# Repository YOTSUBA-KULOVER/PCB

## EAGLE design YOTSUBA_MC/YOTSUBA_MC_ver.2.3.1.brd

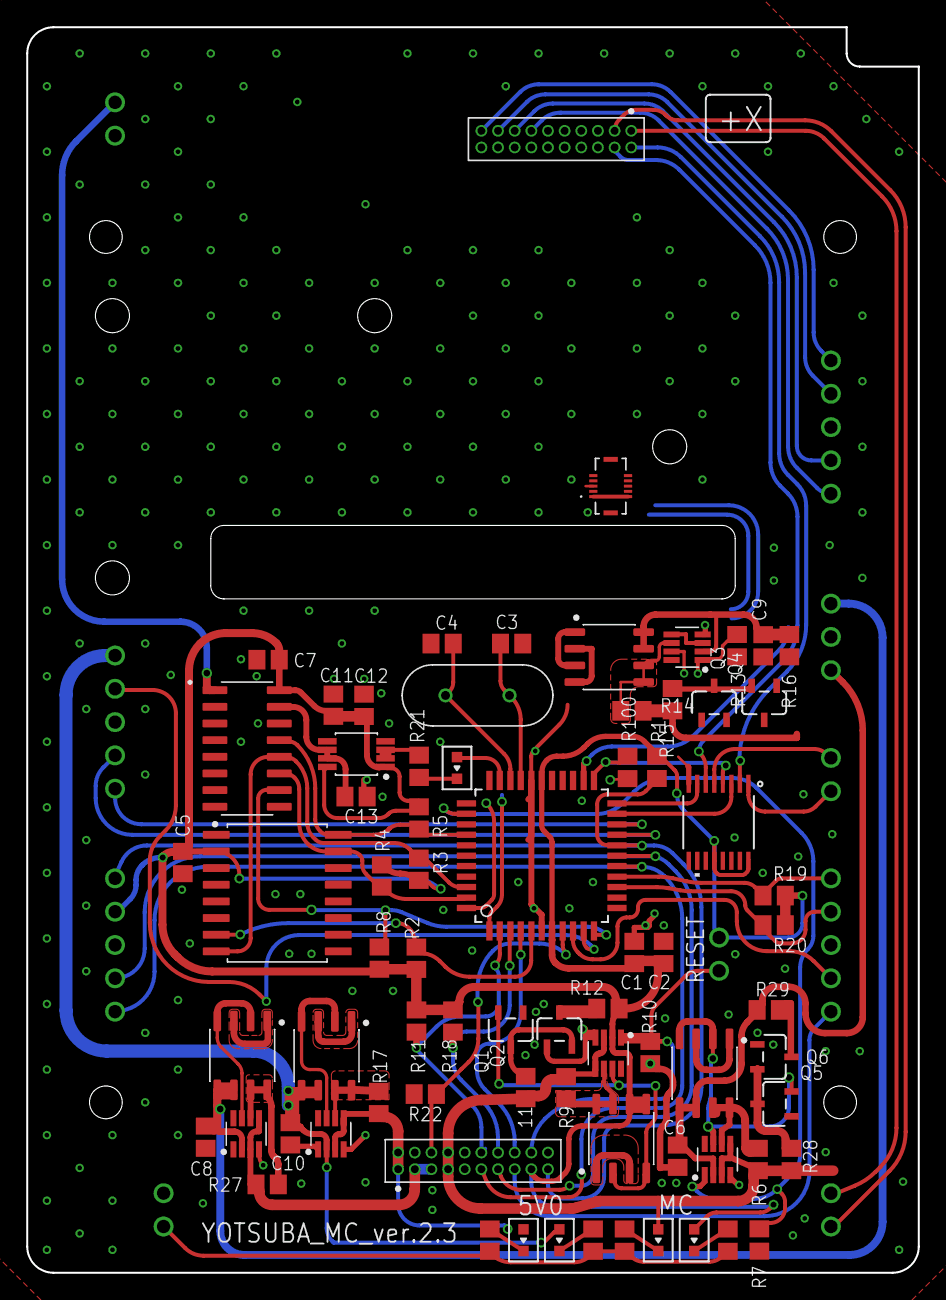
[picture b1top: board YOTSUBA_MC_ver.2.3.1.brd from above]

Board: 2 copper layers, 68.0 x 95.0 mm, 84 parts (0 on the bottom side), 78 nets.

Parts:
11: R2012
C1, C2, C3, C4, C5, C6, C7, C8, C10, C11, C12, C13: 10μ; C2012
C9: 10μ; R2012
COM_MAG: 1X05
IND: 1X02
J1: DF37NB-10DS-0.4V(51); HRS_DF37NB-10DS-0.4V(51)
JP4: 1X02
MAG_PWR: 1X03
PANEL: 1X05
PROGRAM: 1X05
Q1, Q2, Q3, Q4, Q5, Q6: BSS138BKT116SOT23_BSS138_ROM-M; SOT23_BSS138_ROM-M
R1, R2, R3, R4, R5, R6, R7, R8, R10, R11, R12, R13, R14, R15, R16, R17, R18, R19, R20, R21, R22, R23, R24, R25, R26, R27, R28, R29: R2012
R9: 0.025; R2012
R100: 100k; R2012
RPI: 1X05
U1: MAX4702EUE+; 21-0066J_16
U2: MCP3208-CI/SL; SOIC127P600X175-16N
U$1: MT25QL512_16SOP2; SOIC127P1032X265-16N
U$2, U$7, U$9, U$10, U$13: DMG6898LSD; SOIC127P600X150-8N
U$3, U$8, U$11, U$12, U$14: LTC4361; SOP65P280X100-8N
U$4: PIC18LF4620-I/PT; QFP80P1200X1200X120-44N
U$16, U$20, U$26: 1X02
U$17, U$22: M50-3001045
U$18, U$21, U$23, U$24, U$25: LED_1608
U$19: ADR35XX; SOP65P490X110-8N
Y1: HC-49/U-S16000000ABJB; XTAL_HC49P488W43L1150T466H350

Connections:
3V3: 11.1, R6.2, R9.2, R14.2, R15.1, R28.1, U$3.GATEP, U$3.IN, U$8.GATEP, U$8.IN, U$11.GATEP, U$11.IN, U$17.7, U$17.8, U$23.A
3V3_MAG: C6.2, MAG_PWR.1, R29.1, U$2.D1$1, U$2.D1$2, U$3.OUT
3V3_MC_EL: C1.1, C2.1, C5.2, C7.2, C11.2, C12.2, JP4.1, PROGRAM.2, R1.2, R2.2, R3.2, R4.2, R5.2, R8.1, R11.2, R12.1, R18.2, R19.2, R20.2, U1.12, U1.16, U2.16, U$1.VCC, U$4.7, U$4.28, U$7.D1$1, U$7.D1$2, U$8.OUT, U$17.17, U$19.ENABLE, U$19.VIN, U$21.A
3V3_MC_GNSS: C9.2, J1.1, J1.2, R16.1, U$10.D2$1, U$10.D2$2, U$11.OUT
5V0: R17.2, U$14.GATEP, U$14.IN, U$17.1, U$17.2, U$25.A
5V0_MC_RPI: C10.2, RPI.1, U$13.D1$1, U$13.D1$2, U$14.OUT, U$24.A
7V0: R27.2, U$12.GATEP, U$12.IN, U$17.3, U$17.5
7V0_MAG: C8.2, MAG_PWR.3, U$9.D1$1, U$9.D1$2, U$12.OUT
CS_ADC: R8.2, U2.10, U$4.11
GND: C1.2, C2.2, C3.2, C4.2, C5.1, C6.1, C7.1, C8.1, C9.1, C10.1, C11.1, C12.1, C13.2, COM_MAG.3, IND.2, J1.4, J1.6, J1.8, J1.S1, J1.S2, MAG_PWR.2, PANEL.3, PROGRAM.3, Q1.1, Q2.1, Q3.1, Q4.1, Q5.1, Q6.1, R7.2, R10.2, R13.2, R21.1, R22.1, R100.1, RPI.3, U1.8, U2.9, U2.14, U$1.VSS, U$3.GND, U$4.6, U$4.29, U$8.GND, U$11.GND, U$12.GND, U$12.ON, U$14.GND, U$14.ON, U$17.4, U$17.9, U$17.10, U$19.GND_FORCE, U$19.GND_SENSE, U$22.5, U$22.6, U$22.7, U$22.8, U$22.9, U$22.10, U$22.11, U$22.12, U$22.14, U$22.16, U$22.18, U$22.20, U$26.2
INDI: U$4.32, U$18.A
INT<<MAG: COM_MAG.2, U$4.9
INT<<MAIN: R22.2, U$4.8, U$17.6
INT<<RPI: RPI.2, U$4.10
INT>>MAIN: U$4.4, U$17.16
MCLR_MAG: PANEL.5, U$22.19
MCLR_MC: PROGRAM.1, R1.1, U$4.18, U$17.19
MC_SPI_CLK: R5.1, U2.13, U$1.C, U$4.37
MC_SPI_MISO: R3.1, U2.12, U$1.DQ1, U$4.42
MC_SPI_MOSI: R4.1, U2.11, U$1.DQ0, U$4.43
unnamed: R23.2, U$21.C
unnamed: C3.1, U$4.30, Y1.2
unnamed: R24.2, U$23.C
unnamed: C4.1, U$4.31, Y1.1
unnamed: R25.2, U$24.C
unnamed: R26.2, U$25.C
unnamed: R2.1, U$1.S#, U$4.5
unnamed: IND.1, R23.1, R24.1, R25.1, R26.1
unnamed: U$2.S1, U$2.S2
unnamed: R6.1, U$2.D2$1, U$2.D2$2, U$3.SENSE
unnamed: Q5.2, U$2.G1, U$2.G2, U$3.GATE
unnamed: Q5.3, Q6.2, R28.2
unnamed: U$9.S1, U$9.S2
unnamed: R21.2, U$18.C
unnamed: R27.1, U$9.D2$1, U$9.D2$2, U$12.SENSE
unnamed: U$9.G1, U$9.G2, U$12.GATE
unnamed: Q6.3, R29.2
unnamed: U$7.S1, U$7.S2
unnamed: R9.1, U$7.D2$1, U$7.D2$2, U$8.SENSE
unnamed: Q1.2, U$7.G1, U$7.G2, U$8.GATE
unnamed: 11.2, Q1.3, Q2.2
unnamed: Q2.3, R12.2
unnamed: U$10.S1, U$10.S2
unnamed: R14.1, U$10.D1$1, U$10.D1$2, U$11.SENSE
unnamed: Q3.2, U$10.G1, U$10.G2, U$11.GATE
unnamed: Q3.3, Q4.2, R15.2
unnamed: Q4.3, R16.2
unnamed: U$13.S1, U$13.S2
unnamed: R17.1, U$13.D2$1, U$13.D2$2, U$14.SENSE
unnamed: U$13.G1, U$13.G2, U$14.GATE
OUT0_ADC: U2.1, U$26.1
PGC_MAG: PANEL.1, U$22.13
PGC_MC: PROGRAM.5, U$4.16, U$17.11
PGD_MAG: PANEL.2, U$22.15
PGD_MC: PROGRAM.4, U$4.17, U$17.13
RESET_MAG: COM_MAG.1, U$17.15
RESET_MAG_EXT: R7.1, U$3.ON, U$4.35
RESET_MC_EL: JP4.2, R10.1, U$8.ON, U$17.18
RESET_MC_GNSS: R13.1, U$4.24, U$11.ON
RPI_EPS_IO_1: U$20.1, U$22.1
RPI_EPS_IO_2: U$20.2, U$22.3
RX_GNSS: J1.3, U$4.44
RX_MC_TX_MAG: COM_MAG.4, R20.1, U$4.14
RX_MC_TX_MAIN: R18.1, U$4.3, U$17.14
RX_MC_TX_RPI: RPI.4, U$4.19
SELECT: R100.2, U1.4, U$4.23
TRCLK>>COM: U1.2, U$22.2
TRCLK_MC: U1.3, U$4.21
TRCLK_RPI: U1.1, U$16.1
TRDAT>>COM: U1.6, U$22.4
TRDAT_MC: U1.7, U$4.22
TRDAT_RPI: U1.5, U$16.2
TX_GNSS: J1.5, U$4.1
TX_MC_RX_MAG: COM_MAG.5, R19.1, U$4.15
TX_MC_RX_MAIN: R11.1, U$4.2, U$17.12
TX_MC_RX_RPI: RPI.5, U$4.20
VDD_MAG: PANEL.4, U$22.17
VREF_2V5: C13.1, U2.15, U$19.VOUT_FORCE, U$19.VOUT_SENSE

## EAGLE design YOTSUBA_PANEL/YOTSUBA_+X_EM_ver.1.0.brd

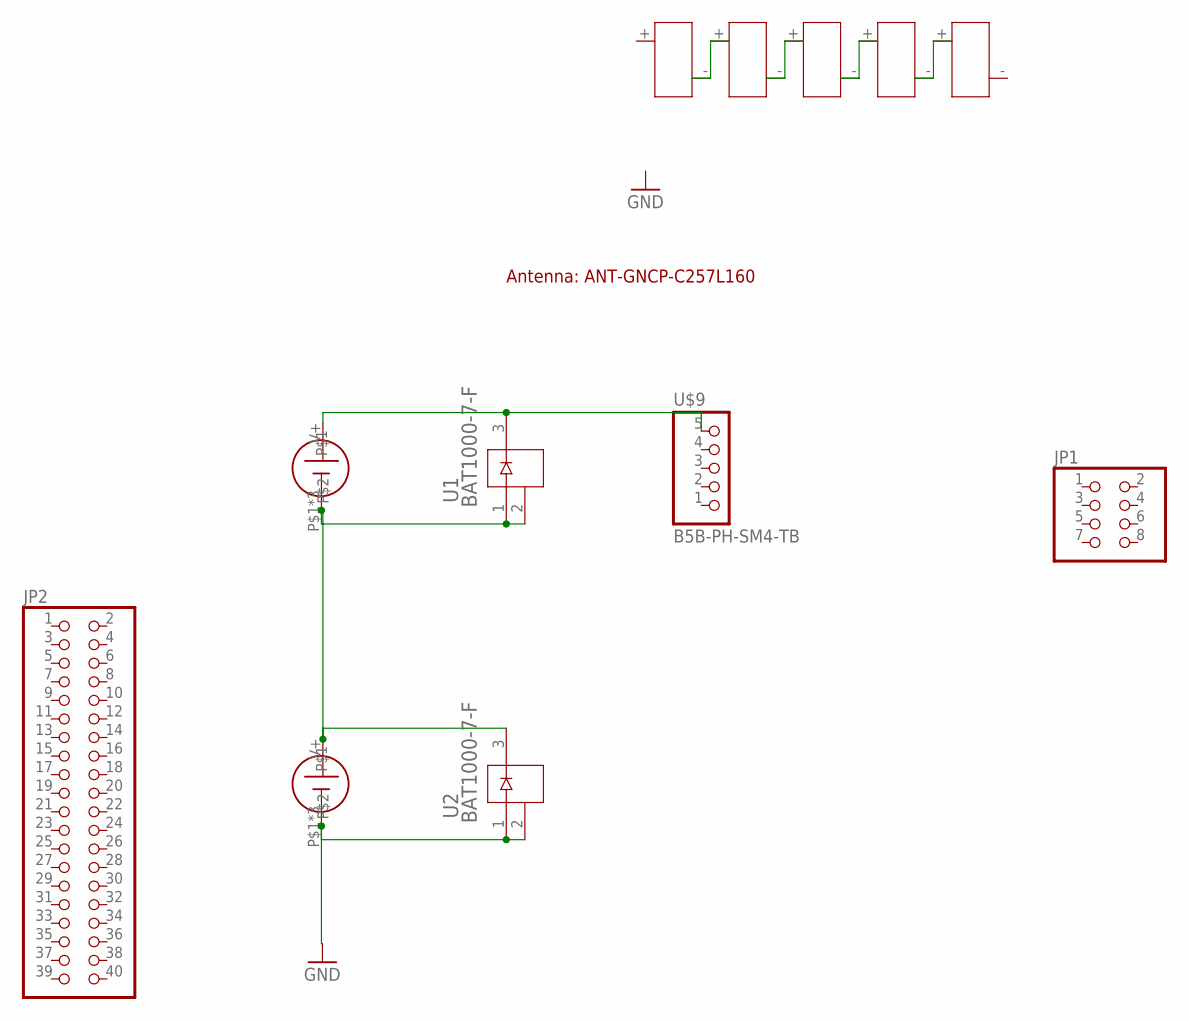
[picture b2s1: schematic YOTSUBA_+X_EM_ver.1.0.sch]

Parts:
JP1: PINHD-2X4; 2X04
JP2: PINHD-2X20; 2X20
U1, U2: BAT1000-7-F; SOT23_BAT_DIO
U$1, U$8: SOLAR_2.0_SOLAR
U$2: ANT-GNCP-C257L160
U$3, U$4, U$5, U$6, U$7: KSP-F12
U$9: B5B-PH-SM4-TB

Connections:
GND: U2.1, U2.2, U$8.P$1, U$8.P$2, U$8.P$3
unnamed: U$3.-, U$4.+
unnamed: U$4.-, U$5.+
unnamed: U$5.-, U$6.+
unnamed: U$6.-, U$7.+
unnamed: U1.1, U1.2, U2.3, U$1.P$1, U$1.P$2, U$1.P$3, U$8.V+
unnamed: U1.3, U$1.V+, U$9.5

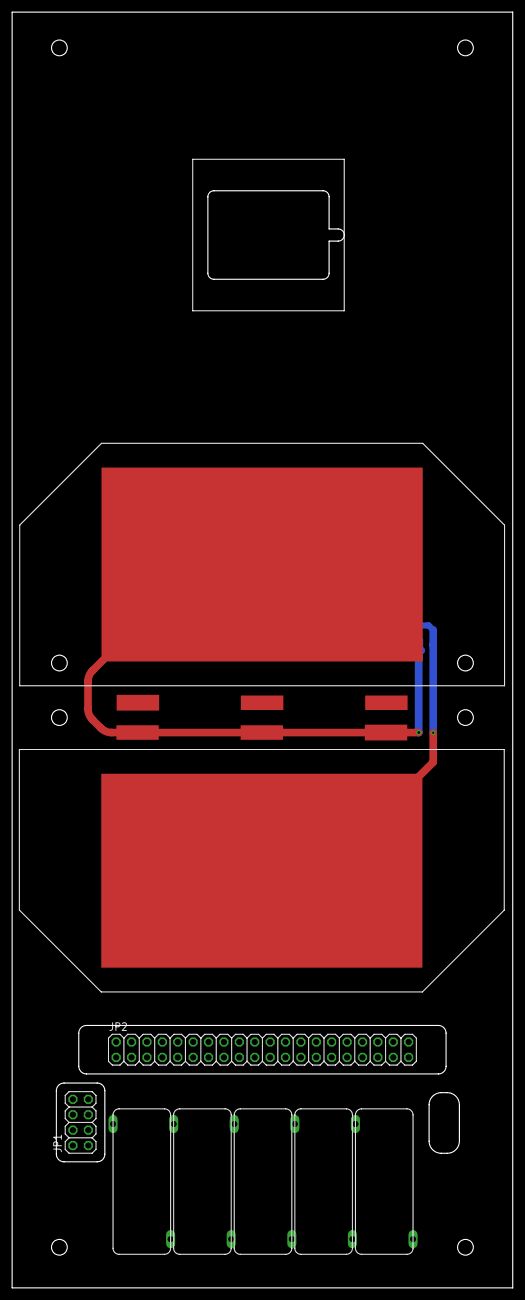
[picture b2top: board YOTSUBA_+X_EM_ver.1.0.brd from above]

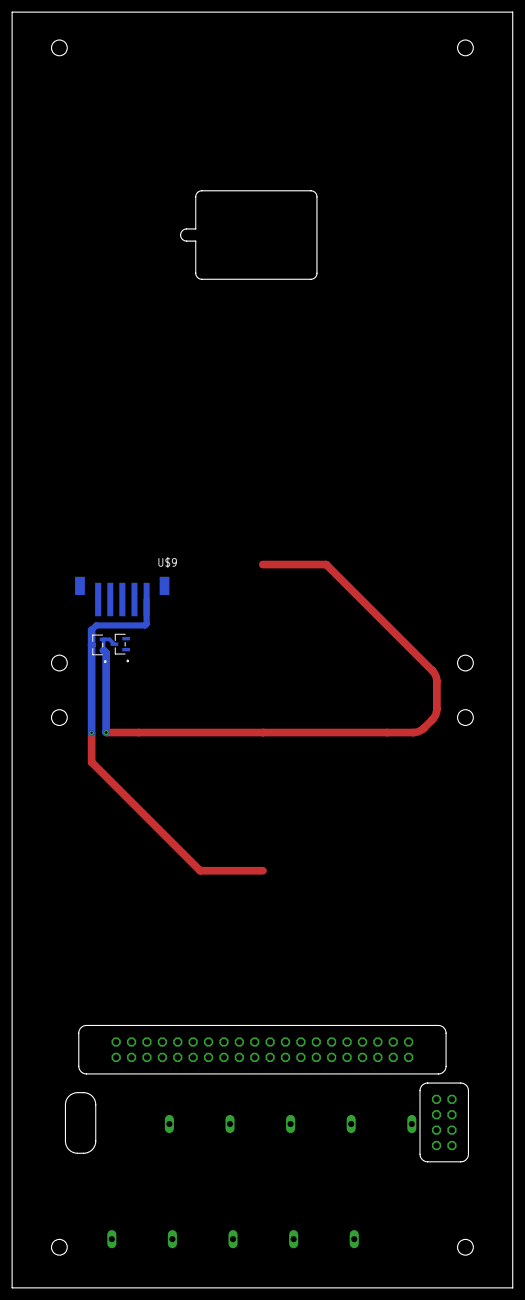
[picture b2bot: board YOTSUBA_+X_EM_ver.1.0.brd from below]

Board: 2 copper layers, 82.6 x 210.5 mm, 13 parts (3 on the bottom side), 7 nets.

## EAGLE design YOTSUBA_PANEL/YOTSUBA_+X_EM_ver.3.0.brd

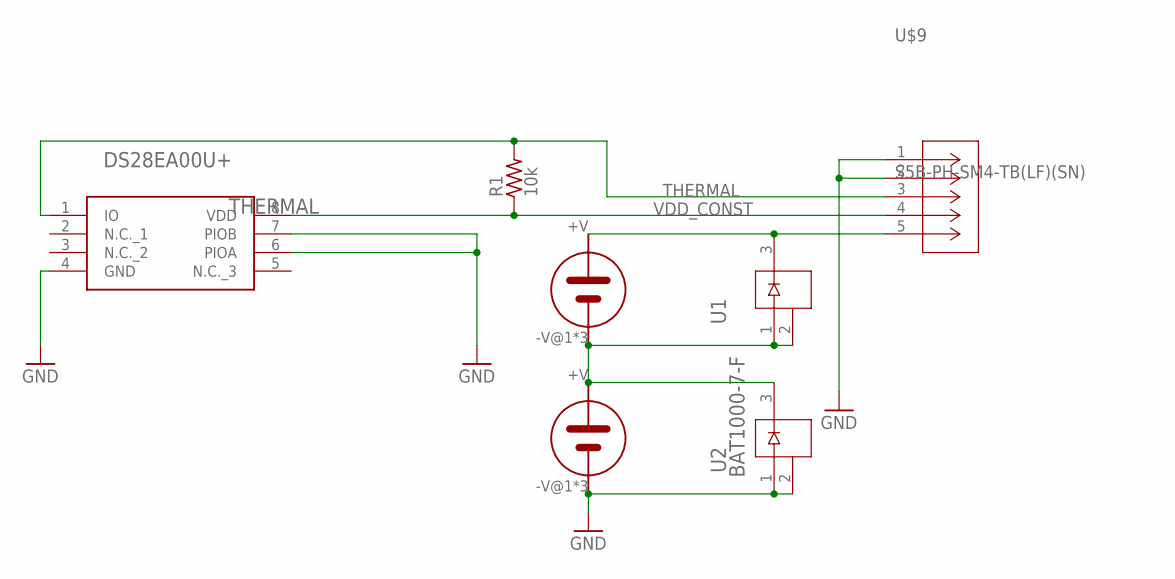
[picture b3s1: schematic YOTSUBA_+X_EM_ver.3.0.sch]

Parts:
R1: 10k; R0805
THERMAL: DS28EA00U+; SOP65P490X110-8N
U1, U2: BAT1000-7-F; SOT23_BAT_DIO
U$2, U$3: 3G30A; SOLAR_3G30A
U$9: S5B-PH-SM4-TB(LF)(SN); CONN_S5B-PH-SM4-TB_JST

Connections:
GND: THERMAL.4 (GND), THERMAL.6 (PIOA), THERMAL.7 (PIOB), U2.1, U2.2, U$3.-V@1 (-V), U$3.-V@2 (-V), U$3.-V@3 (-V), U$9.1, U$9.2
unnamed: U1.1, U1.2, U2.3, U$2.-V@1 (-V), U$2.-V@2 (-V), U$2.-V@3 (-V), U$3.+V
unnamed: U1.3, U$2.+V, U$9.5
THERMAL: R1.2, THERMAL.1 (IO), U$9.3
VDD_CONST: R1.1, THERMAL.8 (VDD), U$9.4

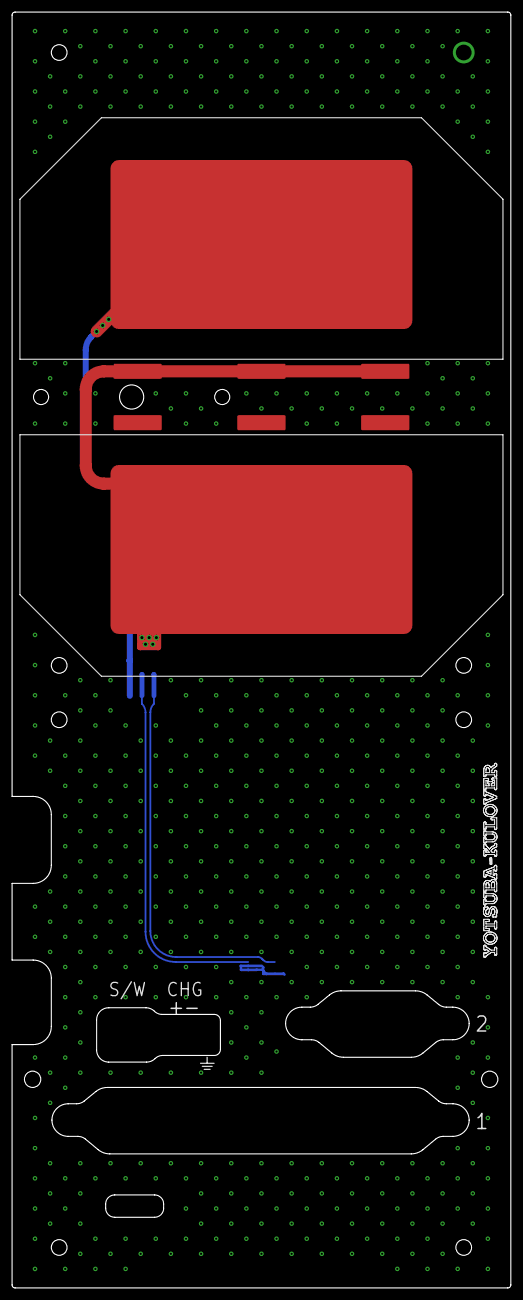
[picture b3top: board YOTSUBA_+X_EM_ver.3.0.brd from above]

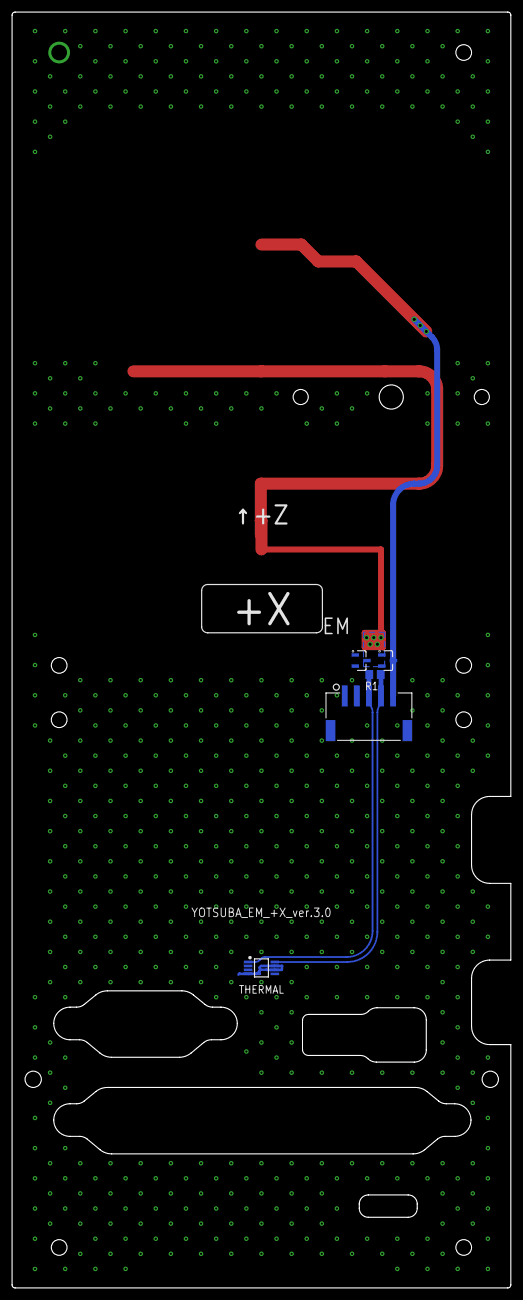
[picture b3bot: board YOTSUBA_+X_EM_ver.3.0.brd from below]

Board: 2 copper layers, 82.6 x 211.3 mm, 8 parts (5 on the bottom side), 5 nets.

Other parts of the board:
U$4: YOTSUBA_NAME

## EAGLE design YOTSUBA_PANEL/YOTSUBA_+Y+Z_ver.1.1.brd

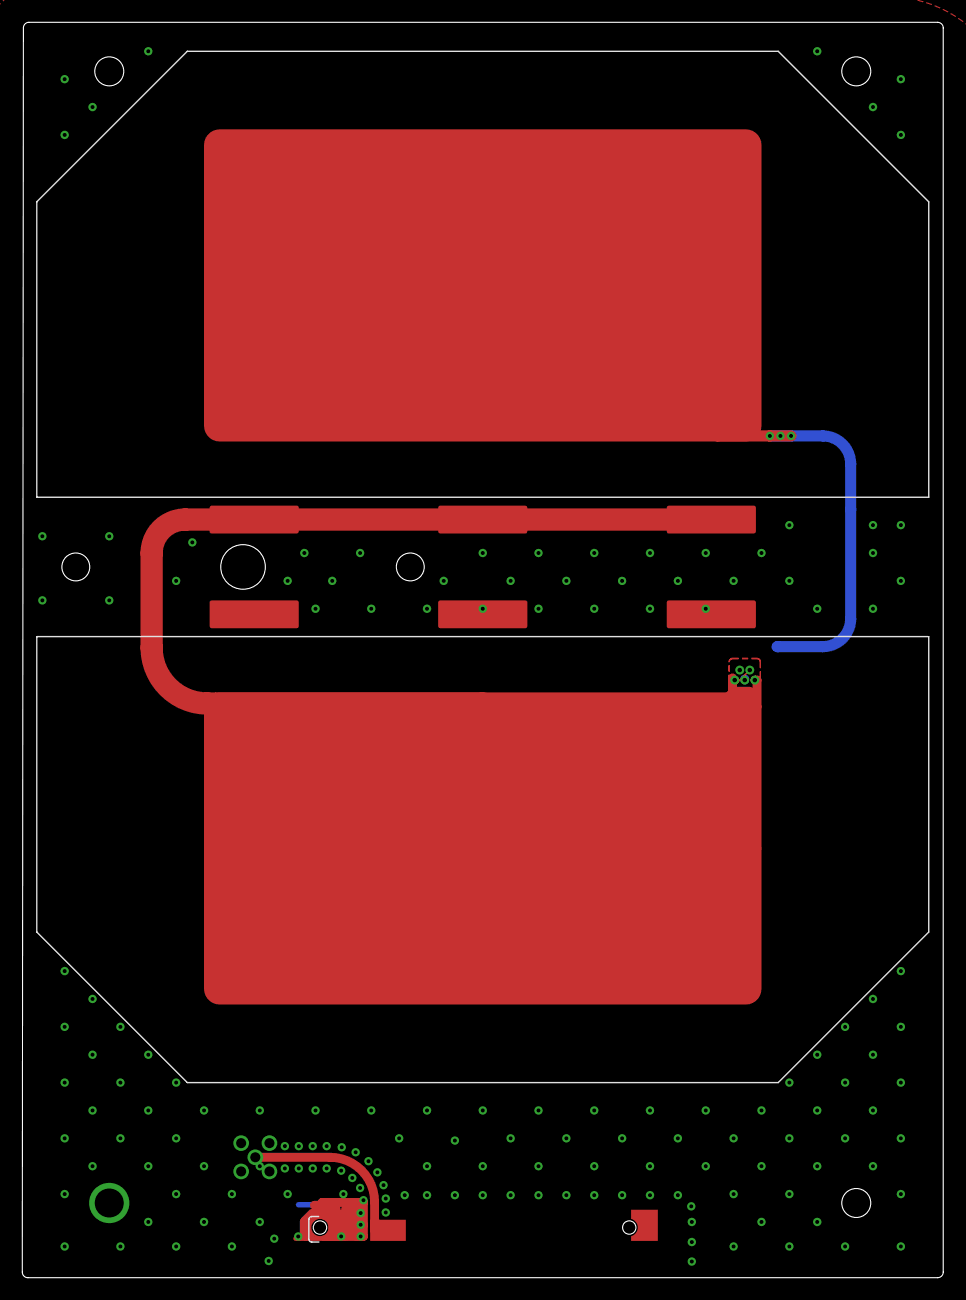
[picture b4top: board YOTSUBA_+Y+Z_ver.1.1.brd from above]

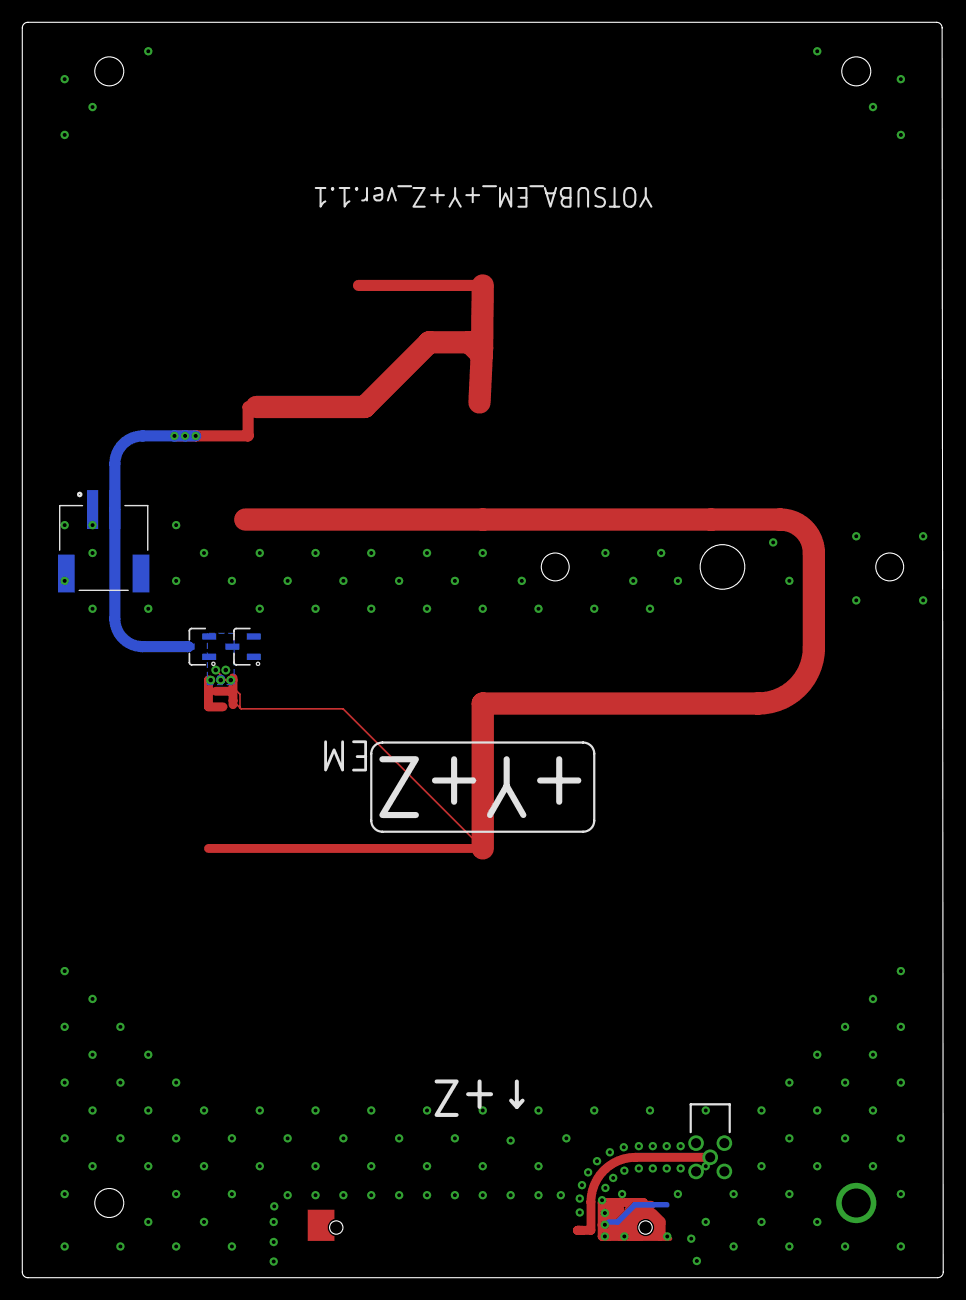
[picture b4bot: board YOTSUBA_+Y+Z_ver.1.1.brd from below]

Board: 2 copper layers, 82.6 x 112.6 mm, 7 parts (4 on the bottom side), 4 nets.

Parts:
ANT1: 1002427; ANTENNA_1002427
J1: MMCX-LR-PC-1_40_; MMCXLRPC140
J2: S2B-PH-SM4-TB(LF)(SN); JST_S2B-PH-SM4-TB(LF)(SN)
U1, U2: BAT1000-7-F; SOT23_BAT_DIO
U$2, U$3: 3G30A; SOLAR_3G30A

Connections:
GND: ANT1.2, J1.2, J1.3, J1.4, J1.5, J2.1, J2.S1, J2.S2, U2.1, U2.2, U$3.-V@1, U$3.-V@2, U$3.-V@3
unnamed: U1.1, U1.2, U2.3, U$2.-V@1, U$2.-V@2, U$2.-V@3, U$3.+V
unnamed: J2.2, U1.3, U$2.+V
RF2: ANT1.1, J1.1

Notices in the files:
parts and their libraries:
COPYRIGHT: Copyright (C) 2023 Ultra Librarian. All rights reserved.
COPYRIGHT: Copyright (C) 2022 Ultra Librarian. All rights reserved.
